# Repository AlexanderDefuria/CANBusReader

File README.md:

# CAN Bus Reader Board

Horrible naming scheme but it is what is at this point.

This project is primarily to integrate Balluf sensors into the CANBus of a FRC Robot.

### Useful Links
This was a learning process...
- [What is nested vector interrupt control (NVIC)?](https://www.motioncontroltips.com/what-is-nested-vector-interrupt-control-nvic/)
- [RP Pico HAL](https://github.com/rp-rs/rp-hal-boards/tree/main/boards/rp-pico)
- [An incorrect approach to PIO with RTIC](https://github.com/sonnny/rtic_template)
- [Very useful PICO HAL with RTIC (Slightly outdated)](Slightly outdated but still very useful RTIC PICO hal impl)

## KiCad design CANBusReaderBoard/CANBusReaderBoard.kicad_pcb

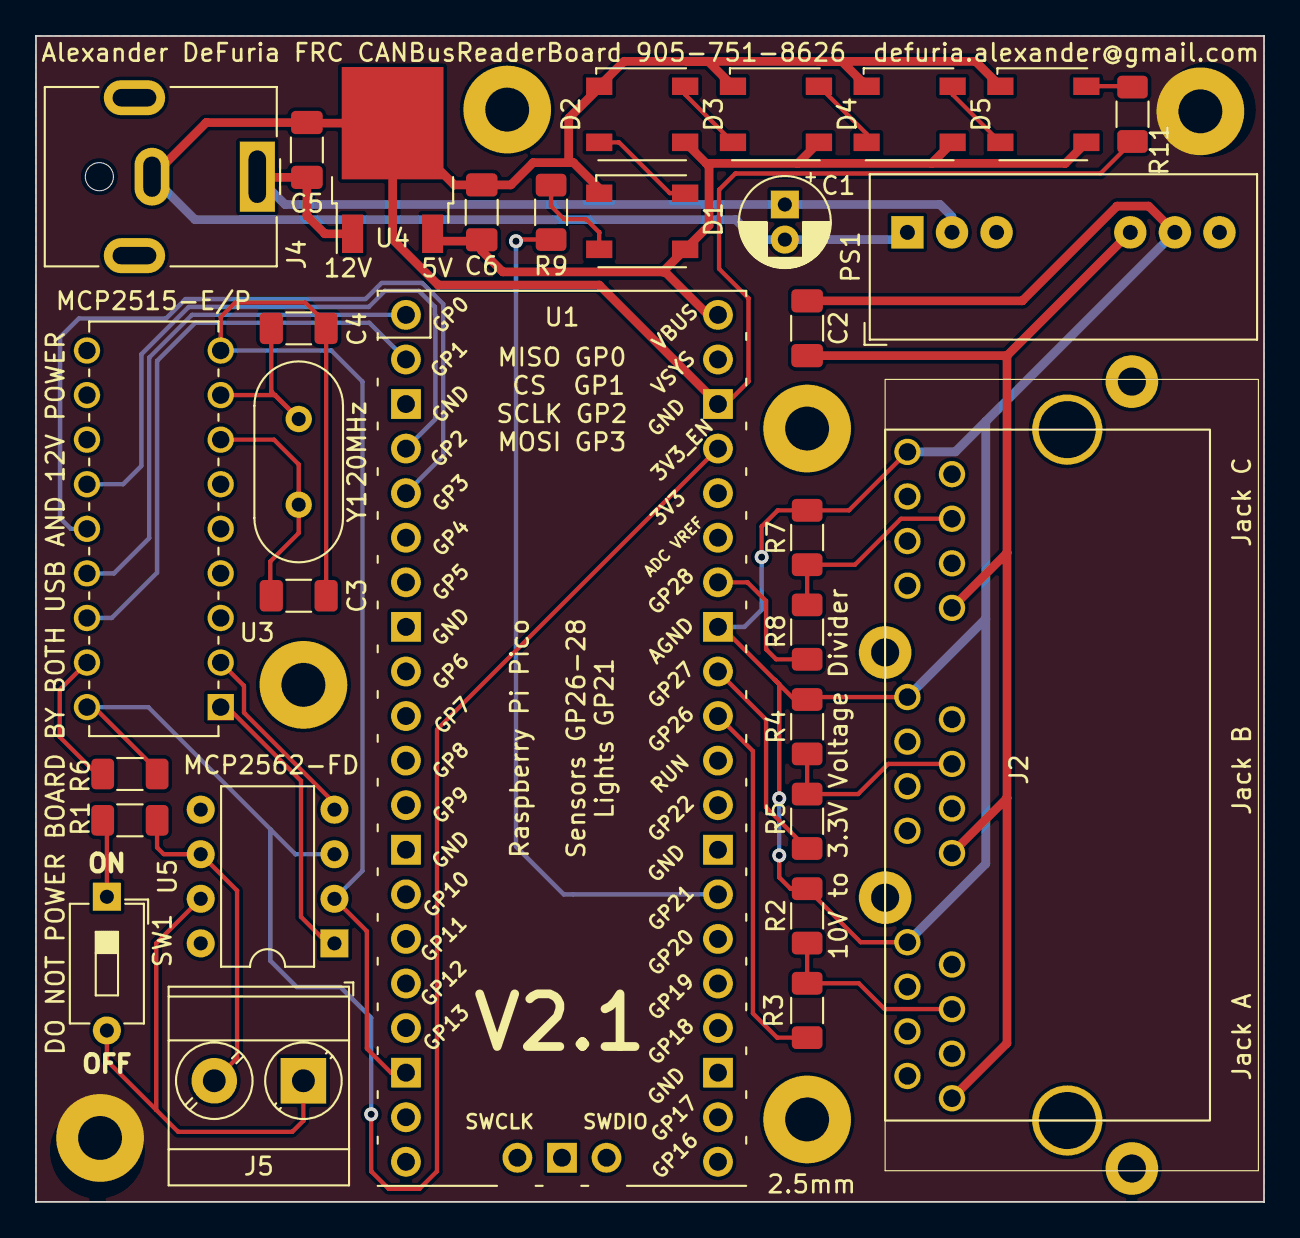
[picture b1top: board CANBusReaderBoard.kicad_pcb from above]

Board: 2 copper layers, 70.0 x 66.4 mm, 31 parts (0 on the bottom side), 32 nets.

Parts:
C1: 100μF; CP_Radial_D5.0mm_P2.00mm
C2, C5, C6: 10μF; C_1206_3216Metric_Pad1.33x1.80mm_HandSolder
C3, C4: 15 pF; C_1206_3216Metric_Pad1.33x1.80mm_HandSolder
D1, D2, D3, D4, D5: Inolux_IN-PI554FCH; LED_Inolux_IN-PI554FCH_PLCC4_5.0x5.0mm_P3.2mm
J2: 3xRJ45V
J4: Jack-DC; BarrelJack_CUI_PJ-063AH_Horizontal
J5: Terminate CAN; TerminalBlock_Phoenix_MKDS-3-2-5.08_1x02_P5.08mm_Horizontal
PS1: ITQ4805SA-H; Converter_DCDC_XP_POWER-ITQxxxxS-H_THT
R1: 10K; R_1206_3216Metric_Pad1.30x1.75mm_HandSolder
R2, R4, R7: 3.3; R_1206_3216Metric_Pad1.30x1.75mm_HandSolder
R3, R5, R8: 6.8; R_1206_3216Metric_Pad1.30x1.75mm_HandSolder
R6: 120k; R_1206_3216Metric_Pad1.30x1.75mm_HandSolder
R9, R11: 499; R_1206_3216Metric_Pad1.30x1.75mm_HandSolder
SW1: SW_DIP_x01; SW_DIP_SPSTx01_Slide_6.7x4.1mm_W7.62mm_P2.54mm_LowProfile
U1: Pico; RPi_Pico_StandOffs
U3: MCP2515-E/P; MCP2515-E&slash_P
U4: NCV5501DT50RKG; TO-252-2
U5: MCP2562-E-P; DIP-8_W7.62mm
Y1: Crystal 20Mhz; Crystal_HC49-4H_Vertical

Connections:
+3V3: R1.1, U1.37 (3V3_EN), U3.18 (VDD), U5.3 (VDD)
+5V: C6.1, D1.3 (VDD), D2.3 (VDD), D3.3 (VDD), D4.3 (VDD), D5.3 (VDD), U1.40 (VBUS), U4.1 (OUT)
+12V: C1.1, C5.1, J4.1, PS1.2 (+Vin), U4.3 (IN)
+24V: C2.1, J2.A1, J2.B1, J2.C1, PS1.6 (+Vout)
AGND: C2.2, J2.A8, J2.B8, J2.C8, PS1.7 (-Vout), R2.1, R4.1, R7.1, U1.33 (AGND)
CANH: J5.1, SW1.2, U5.7 (CANH)
CANL: J5.2, R6.2, U5.6 (CANL)
CS: U1.2 (GPIO1), U3.16 (*CS)
GND3: C3.1, C4.1, U1.18 (GND), U3.9 (VSS), U5.2 (VSS)
GNDREF: C1.2, C5.2, C6.2, D1.1 (VSS), D2.1 (VSS), D3.1 (VSS), D4.1 (VSS), D5.1 (VSS), J4.2, PS1.1 (-Vin), R11.2, U1.38 (GND), U4.2 (GND)
LED1: R9.1, U1.27 (GPIO21)
MISO: U1.1 (GPIO0), U3.15 (SO)
MOSI: U1.5 (GPIO3), U3.14 (SI)
unnamed: C3.2, U3.7 (OSC2), Y1.2
unnamed: C4.2, U3.8 (OSC1), Y1.1
unnamed: D1.2 (DIN), R9.2
unnamed: D1.4 (DO), D2.2 (DIN)
unnamed: D2.4 (DO), D3.2 (DIN)
unnamed: D3.4 (DO), D4.2 (DIN)
unnamed: D4.4 (DO), D5.2 (DIN)
unnamed: D5.4 (DO), R11.1
unnamed: R1.2, U3.17 (*RESET)
unnamed: R6.1, SW1.1
RX: U3.2 (RXCAN), U5.4 (RXD)
SCLK: U1.4 (GPIO2), U3.13 (SCK)
SENSOR 0: R3.2, U1.31 (GPIO26_ADC0)
SENSOR 0 (24V): J2.A5, R2.2, R3.1
SENSOR 1: R5.2, U1.32 (GPIO27_ADC1)
SENSOR 1 (24V): J2.B5, R4.2, R5.1
SENSOR 2: R8.2, U1.34 (GPIO28_ADC2)
SENSOR 2 (24V): J2.C5, R7.2, R8.1
TX: U3.1 (TXCAN), U5.1 (TXD)

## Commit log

2022-09-14 init
2022-09-14 printed board version
2022-09-26 Started new design using RP2040 Chip
2022-10-01 Components all added, need to figure out RP2040 Powering and supplemental components.
2022-10-02 voltage regultor to 3.3v
2022-10-12 Working on status leds now
2022-10-14 cahnged to pico from rp2040
2022-10-19 libs
2022-10-20 ready for wiring
2022-10-20 Finished footprints and started initial track laying
2022-11-30 printed
2022-12-29 Restructured
2023-01-01 code init
2023-01-01 rename reademe to readme
